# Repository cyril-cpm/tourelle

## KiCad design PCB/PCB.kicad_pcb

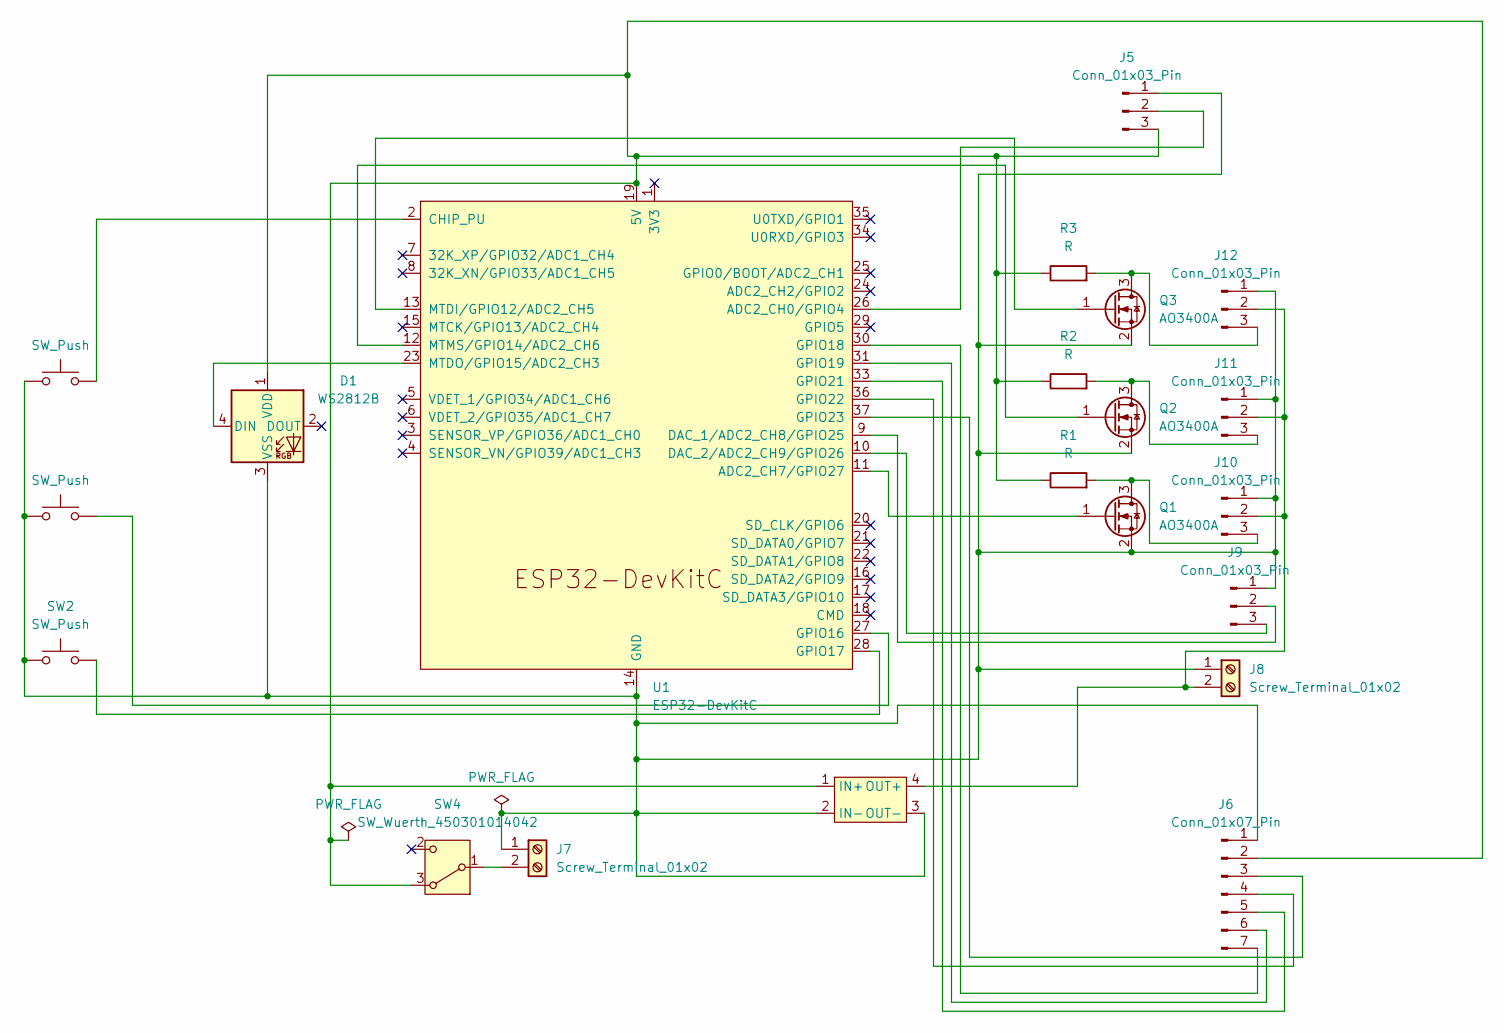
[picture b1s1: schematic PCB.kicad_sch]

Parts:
D1: WS2812B; LED_WS2812B-2020_PLCC4_2.0x2.0mm
J5, J9, J10, J11, J12: Conn_01x03_Pin; JST_XH_S3B-XH-A-1_1x03_P2.50mm_Horizontal
J6: Conn_01x07_Pin; JST_XH_S7B-XH-A-1_1x07_P2.50mm_Horizontal
J7, J8: Screw_Terminal_01x02; TerminalBlock_Phoenix_MKDS-1,5-2_1x02_P5.00mm_Horizontal
Q1, Q2, Q3: AO3400A; SOT-23_Handsoldering
R1, R2, R3: R; R_1206_3216Metric_Pad1.30x1.75mm_HandSolder
SW1, SW2, SW3: SW_Push; SW_PUSH_6mm_H5mm
SW4: SW_Wuerth_450301014042; SW_Slide-03_Wuerth-WS-SLTV_10x2.5x6.4_P2.54mm
U1: ESP32-DevKitC
U2: XL6009_module

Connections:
unnamed: D1.4 (DIN), U1.23 (MTDO/GPIO15/ADC2_CH3)
unnamed: D1.1 (VDD), J5.3, J6.2, R1.1, R2.1, R3.1, SW4.3 (A), U1.19 (5V), U2.1 (IN+)
unnamed: D1.3 (VSS), J5.1, J6.1, J7.1, J8.1, J9.1, J10.1, J11.1, J12.1, Q1.2 (S), Q2.2 (S), Q3.2 (S), SW1.1, SW2.1, SW3.1, U1.14 (GND), U1.32 (GND), U1.38 (GND), U2.2 (IN-), U2.3 (OUT-)
unnamed: J5.2, U1.26 (ADC2_CH0/GPIO4)
unnamed: J6.3, U1.37 (GPIO23)
unnamed: J6.4, U1.36 (GPIO22)
unnamed: J6.5, U1.33 (GPIO21)
unnamed: J6.6, U1.31 (GPIO19)
unnamed: J6.7, U1.30 (GPIO18)
unnamed: J7.2, SW4.1 (B)
unnamed: J9.2, U1.9 (DAC_1/ADC2_CH8/GPIO25)
unnamed: J9.3, U1.10 (DAC_2/ADC2_CH9/GPIO26)
unnamed: J8.2, J10.2, J11.2, J12.2, U2.4 (OUT+)
unnamed: J10.3, Q1.3 (D), R1.2
unnamed: J11.3, Q2.3 (D), R2.2
unnamed: J12.3, Q3.3 (D), R3.2
unnamed: Q1.1 (G), U1.11 (ADC2_CH7/GPIO27)
unnamed: Q2.1 (G), U1.12 (MTMS/GPIO14/ADC2_CH6)
unnamed: Q3.1 (G), U1.13 (MTDI/GPIO12/ADC2_CH5)
unnamed: SW3.2, U1.2 (CHIP_PU)
unnamed: SW1.2, U1.27 (GPIO16)
unnamed: SW2.2, U1.28 (GPIO17)

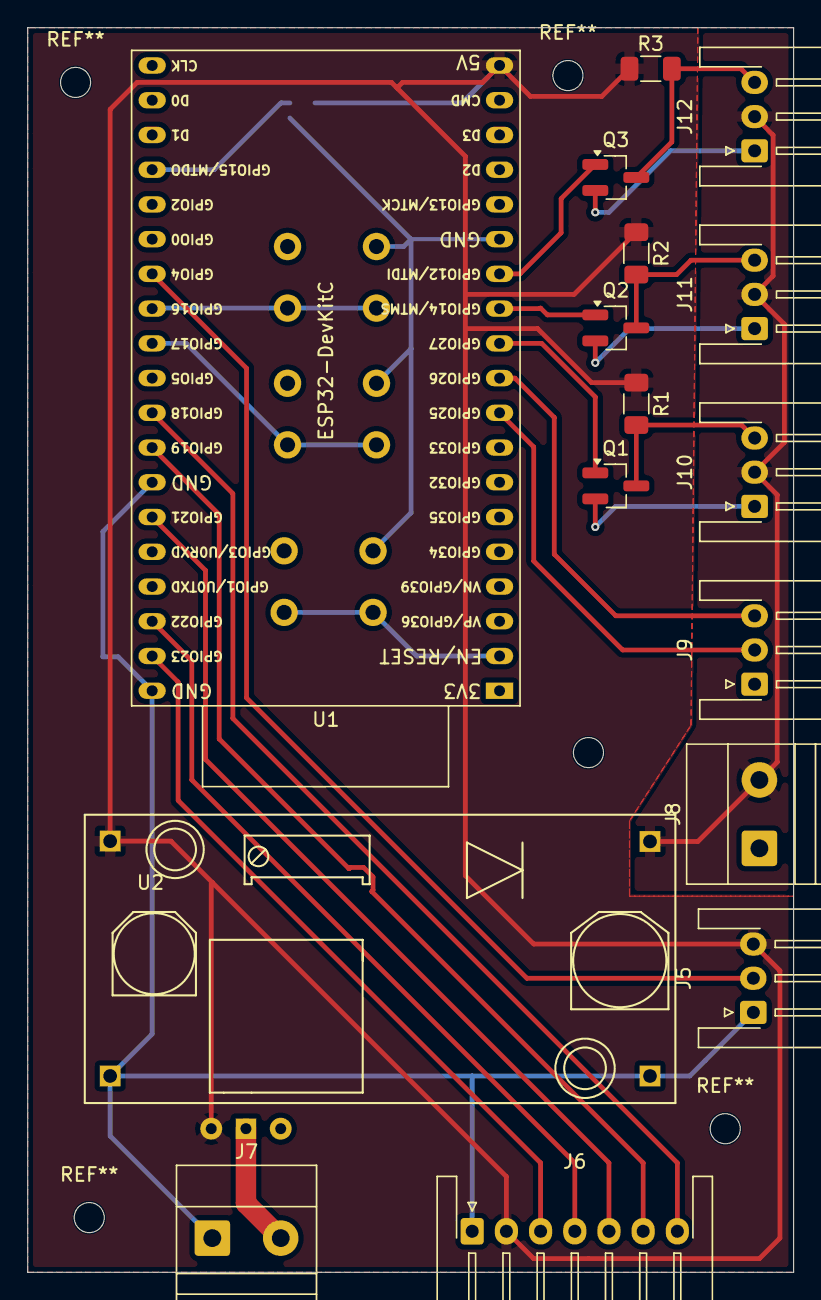
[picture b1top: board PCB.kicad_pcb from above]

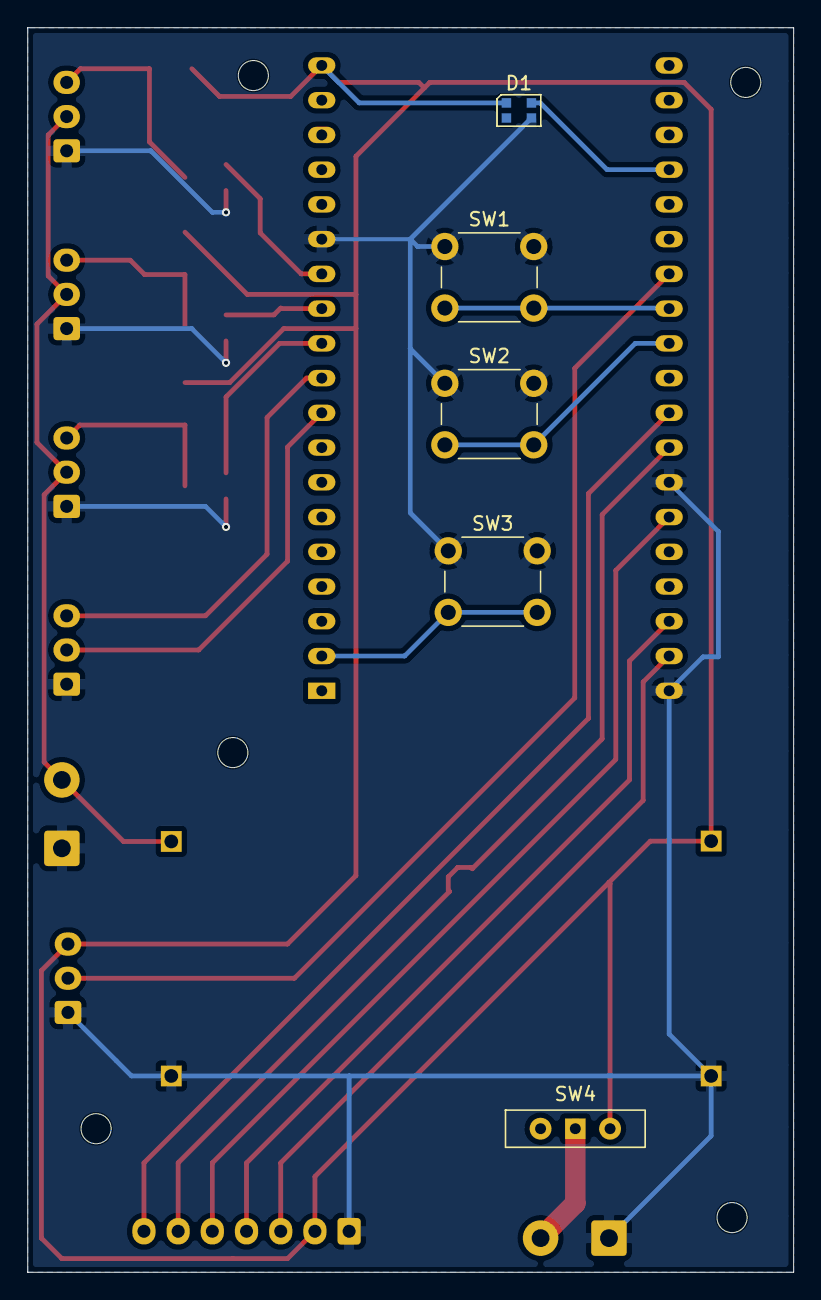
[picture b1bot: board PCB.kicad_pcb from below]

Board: 2 copper layers, 56.0 x 91.0 mm, 21 parts (5 on the bottom side), 22 nets.
